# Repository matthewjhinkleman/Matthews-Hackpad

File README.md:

# Matthews-Hackpad
This is my first project that I am bringing to life thanks to HackClub. It is a macropad that is mainly targeted towards multimedia controls.

BOM:
| Value             | Qty |
|-------------------|-----|
| OLED              | 1   |
| SW_Push           | 6   |
| RotaryEncoder     | 1   |
| XIAO-RP2040-DIP   | 1   |

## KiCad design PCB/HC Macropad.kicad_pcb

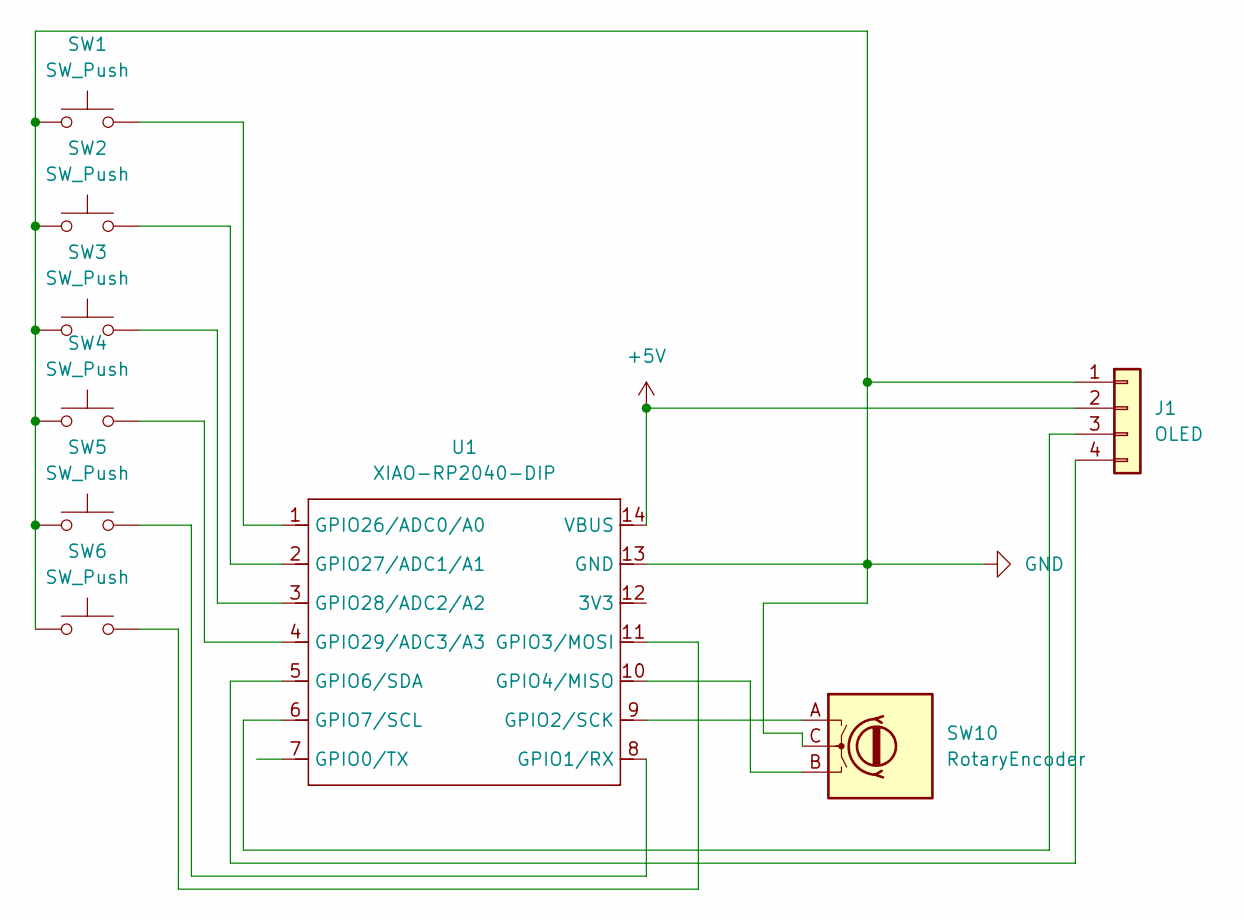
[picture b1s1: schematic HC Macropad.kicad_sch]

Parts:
J1: OLED; SSD1306-0.91-OLED-4pin-128x32
SW1, SW2, SW3, SW4, SW5, SW6: SW_Push; SW_Cherry_MX_1.00u_PCB
SW10: RotaryEncoder; RotaryEncoder_Alps_EC11E_Vertical_H20mm_CircularMountingHol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
U1: XIAO-RP2040-DIP

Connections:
+5V: J1.2 (VCC), U1.14 (VBUS)
GND: J1.1 (GND), SW1.1, SW2.1, SW3.1, SW4.1, SW5.1, SW6.1, SW10.C, U1.13 (GND)
unnamed: J1.3 (SCL), U1.6 (GPIO7/SCL)
unnamed: J1.4 (SDA), U1.5 (GPIO6/SDA)
unnamed: SW5.2, U1.8 (GPIO1/RX)
unnamed: SW10.A, U1.9 (GPIO2/SCK)
unnamed: SW6.2, U1.11 (GPIO3/MOSI)
unnamed: SW10.B, U1.10 (GPIO4/MISO)
unnamed: SW1.2, U1.1 (GPIO26/ADC0/A0)
unnamed: SW2.2, U1.2 (GPIO27/ADC1/A1)
unnamed: SW3.2, U1.3 (GPIO28/ADC2/A2)
unnamed: SW4.2, U1.4 (GPIO29/ADC3/A3)

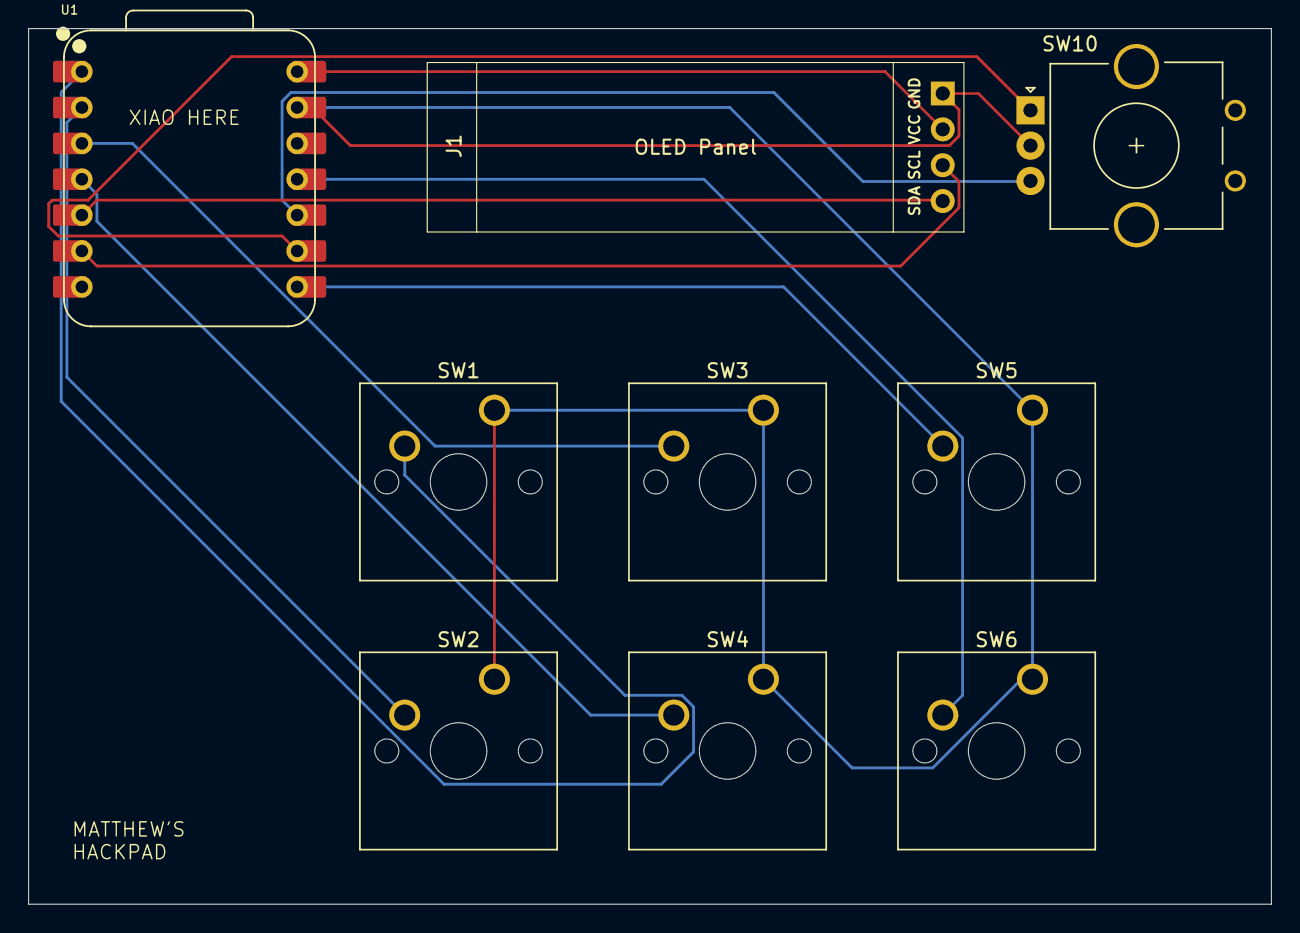
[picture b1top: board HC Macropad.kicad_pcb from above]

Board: 2 copper layers, 88.0 x 62.0 mm, 9 parts (0 on the bottom side), 12 nets.

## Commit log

2025-12-06 Added CAD and PCB Files
2025-12-06 Added firmware
    Made with help of ChatGPT. Haven't decided on what the bottom row of keys does yet so there are just placeholders
